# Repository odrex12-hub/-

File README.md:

//@version=5
indicator("Профессиональный Калькулятор v3.0", shorttitle="ProCalc Pro", overlay=true, max_labels_count=100)

// ========================
// НАСТРОЙКИ ОТОБРАЖЕНИЯ
// ========================
showTable := input.bool(true, "Показать таблицу")
showLabels := input.bool(true, "Показать метки")
showPlots := input.bool(false, "Показать графики")

// ========================
// ВИД КАЛЬКУЛЯТОРА
// ========================
calcType = input.string("Position Size", "🎯 Тип калькулятора", 
     options=["Position Size", "Risk/Reward", "Fibonacci", "Pivot Points", "Volatility", "Margin", "Portfolio Risk"])

// ========================
// ОБЩИЕ НАСТРОЙКИ
// ========================
// Автоматическое определение цен
useCurrentPrices = input.bool(true, "📊 Использовать текущие цены")

// Валютные пары и тип инструмента
instrumentType = input.string("Stock", "Тип инструмента", 
     options=["Stock", "Forex", "Crypto", "Futures", "Options"])

leverage = input.float(1.0, "Кредитное плечо", minval=1.0, maxval=100.0, step=0.5)

// ========================
// 1. УЛУЧШЕННЫЙ КАЛЬКУЛЯТОР РАЗМЕРА ПОЗИЦИИ
// ========================
if calcType == "Position Size"
    // Входные параметры
    depositSize = input.float(10000, "💰 Размер депозита ($)", minval=100, step=100)
    riskPerTrade = input.float(2.0, "⚠️ Риск на сделку (%)", minval=0.1, maxval=100, step=0.1)
    maxPortfolioRisk = input.float(20.0, "Макс. риск портфеля (%)", minval=5, maxval=100)
    
    // Автоматические цены
    autoEntry = useCurrentPrices ? close : na
    autoStop = useCurrentPrices ? low[1] : na
    
    entryPrice = input.float(autoEntry, "🎯 Цена входа", minval=0.00001)
    stopLoss = input.float(autoStop, "🛑 Цена стоп-лосса", minval=0.00001)
    takeProfit = input.float(na, "🎯 Цена тейк-профита", minval=0.00001)
    
    // Комиссии в зависимости от типа инструмента
    commissionType = input.string("Percent", "Тип комиссии", options=["Percent", "Fixed", "PerUnit"])
    
    commissionPercent = input.float(0.1, "Комиссия (%)", minval=0.0, step=0.01)
    commissionFixed = input.float(1.0, "Фиксированная комиссия ($)", minval=0.0, step=0.1)
    commissionPerUnit = input.float(0.01, "Комиссия за единицу", minval=0.0, step=0.001)
    
    // Скользящий стоп
    useTrailingStop = input.bool(false, "Использовать трейлинг-стоп")
    trailingDistance = input.float(2.0, "Дистанция трейлинга (%)", minval=0.1, step=0.1)
    
    // Расчеты с валидацией
    if entryPrice > 0 and stopLoss > 0
        // Проверка корректности входа
        if entryPrice <= stopLoss
            runtime.error("Для лонга цена входа должна быть ВЫШЕ стоп-лосса!")
        
        riskAmount := depositSize * (riskPerTrade / 100)
        priceRisk := math.abs(entryPrice - stopLoss)
        
        // Расчет размера позиции с учетом комиссии
        positionSizeBase := riskAmount / priceRisk
        
        // Учет комиссии
        if commissionType == "Percent"
            commissionCost := positionSizeBase * entryPrice * (commissionPercent / 100)
            effectivePositionSize := positionSizeBase
        else if commissionType == "Fixed"
            commissionCost := commissionFixed
            effectivePositionSize := (riskAmount - commissionCost) / priceRisk
        else
            commissionCost := positionSizeBase * commissionPerUnit
            effectivePositionSize := (riskAmount - commissionCost) / priceRisk
        
        positionSize := math.floor(effectivePositionSize)
        totalCost := positionSize * entryPrice + commissionCost
        positionPercent := (totalCost / depositSize) * 100
        
        // Расчет тейк-профита если задан
        if not na(takeProfit) and takeProfit > 0
            rewardAmount := math.abs(takeProfit - entryPrice) * positionSize
            rrRatio := rewardAmount / riskAmount
            winToBreakEven := (riskAmount / rewardAmount) * 100
        else
            rewardAmount := na
            rrRatio := na
            winToBreakEven := na
        
        // Трейлинг-стоп расчет
        if useTrailingStop
            trailStopPrice := entryPrice * (1 - trailingDistance / 100)
            trailDistance := math.abs(entryPrice - trailStopPrice)
        else
            trailStopPrice := na
        
        // Отображение
        if showLabels
            var label posLabel = label.new(bar_index, high * 1.02, "", 
                 color=color.new(color.blue, 90), textcolor=color.white, 
                 style=label.style_label_center, yloc=yloc.price,
                 size=size.normal)
            
            labelText = "🎯 РАСЧЕТ ПОЗИЦИИ\n" +
                 "═══════════════════\n" +
                 "📊 Тип: " + instrumentType + "\n" +
                 "💰 Депозит: $" + str.tostring(depositSize, "#,##0.00") + "\n" +
                 "⚠️ Риск: " + str.tostring(riskPerTrade, "#.#") + "% ($" + str.tostring(riskAmount, "#,##0.00") + ")\n" +
                 "🎯 Вход: $" + str.tostring(entryPrice, "#,##0." + str.tostring(math.max(2, math.ceil(math.log10(1/entryPrice))))) + "\n" +
                 "🛑 Стоп: $" + str.tostring(stopLoss, "#,##0." + str.tostring(math.max(2, math.ceil(math.log10(1/stopLoss))))) + "\n" +
                 "📈 Размер: " + str.tostring(positionSize, "#,##0") + " ед.\n" +
                 "💵 Стоимость: $" + str.tostring(totalCost, "#,##0.00") + "\n" +
                 "📊 % от депозита: " + str.tostring(positionPercent, "#.#") + "%\n" +
                 "💸 Комиссия: $" + str.tostring(commissionCost, "#,##0.00")
            
            if not na(takeProfit)
                labelText += "\n" +
                     "🎯 Тейк: $" + str.tostring(takeProfit, "#,##0.00") + "\n" +
                     "⚖️ R/R: " + str.tostring(rrRatio, "#.##") + ":1\n" +
                     "📈 Нужно побед: " + str.tostring(winToBreakEven, "#.#") + "%"
            
            if useTrailingStop
                labelText += "\n" +
                     "🎯 Трейлинг: $" + str.tostring(trailStopPrice, "#,##0.00")
            
            label.set_text(posLabel, labelText)
        
        // Табличное отображение
        if showTable
            var table posTable = table.new(position.top_right, 3, 15, 
                 bgcolor=color.new(color.blue, 95),
                 frame_color=color.blue,
                 frame_width=2)
            
            table.cell(posTable, 0, 0, "ПАРАМЕТР", text_color=color.white, bgcolor=color.blue)
            table.cell(posTable, 1, 0, "ЗНАЧЕНИЕ", text_color=color.white, bgcolor=color.blue)
            table.cell(posTable, 2, 0, "МЕТРИКА", text_color=color.white, bgcolor=color.blue)
            
            table.cell(posTable, 0, 1, "Депозит")
            table.cell(posTable, 1, 1, "$" + str.tostring(depositSize, "#,##0"))
            table.cell(posTable, 2, 1, "100%")
            
            table.cell(posTable, 0, 2, "Рик на сделку")
            table.cell(posTable, 1, 2, str.tostring(riskPerTrade, "#.#") + "%")
            table.cell(posTable, 2, 2, "$" + str.tostring(riskAmount, "#,##0"))
            
            table.cell(posTable, 0, 3, "Цена входа")
            table.cell(posTable, 1, 3, "$" + str.tostring(entryPrice, "#,##0.00"))
            table.cell(posTable, 2, 3, "")
            
            // ... и так далее для всех параметров

// ========================
// 2. РАСШИРЕННЫЙ RISK/REWARD
// ========================
else if calcType == "Risk/Reward"
    entryRR = input.float(close, "Цена входа")
    stopRR = input.float(low[1], "Стоп-лосс")
    targets = input.string("3", "Количество целей", options=["1", "2", "3", "4", "5"])
    
    numTargets = str.tonumber(targets)
    targetPrices = array.new_float()
    
    for i = 0 to numTargets - 1
        targetPrice = input.float(close * (1 + (i + 1) * 0.05), "Цель " + str.tostring(i + 1))
        array.push(targetPrices, targetPrice)
    
    risk = math.abs(entryRR - stopRR)
    
    // Расчет вероятности на основе волатильности
    atr20 = ta.atr(20)
    volatilityFactor = atr20 / close
    baseProbability = 0.5 // Базовая вероятность
    
    // Отображение с цветовой индикацией
    if showLabels
        var label rrLabel = label.new(bar_index, high * 1.02, "",
             color=color.new(color.purple, 90), textcolor=color.white,
             style=label.style_label_center, yloc=yloc.price)
        
        labelText = "⚖️ RISK/REWARD АНАЛИЗ\n" +
             "═══════════════════\n" +
             "Риск на сделку: $" + str.tostring(risk, "#.##") + "\n" +
             "ATR (20): " + str.tostring(atr20/close*100, "#.#") + "%\n" +
             "═══════════════════\n"
        
        for i = 0 to numTargets - 1
            targetPrice = array.get(targetPrices, i)
            reward = math.abs(targetPrice - entryRR)
            rrRatio = reward / risk
            probability = baseProbability * (1 / rrRatio) * (1 - volatilityFactor)
            
            // Цвет в зависимости от качества R/R
            rrColor = rrRatio >= 2 ? color.green : rrRatio >= 1.5 ? color.orange : color.red
            
            labelText += "Цель " + str.tostring(i + 1) + ": " + 
                 str.tostring(rrRatio, "#.##") + ":1 | " + 
                 str.tostring(probability * 100, "#.#") + "%\n" +
                 "$" + str.tostring(targetPrice, "#.##") + " (+" + 
                 str.tostring(reward, "#.##") + ")\n"

// ========================
// 6. КАЛЬКУЛЯТОР МАРЖИ (НОВЫЙ)
// ========================
else if calcType == "Margin"
    // Параметры для разных типов инструментов
    marginRequirements = input.float(50.0, "Требование маржи (%)", minval=1.0, maxval=100.0)
    positionMargin = input.float(10000.0, "Маржа позиции ($)", minval=100.0)
    
    // Расчет доступной маржи
    totalMargin = depositSize * leverage
    usedMargin = positionMargin
    freeMargin = totalMargin - usedMargin
    marginLevel = (totalMargin / usedMargin) * 100
    
    // Маржин колл уровни
    marginCallLevel = input.float(100.0, "Уровень маржин колла (%)", minval=50.0)
    stopOutLevel = input.float(50.0, "Уровень стоп-аута (%)", minval=20.0)
    
    // Цветовая индикация
    marginColor = marginLevel > 200 ? color.green : 
                  marginLevel > 150 ? color.orange : 
                  marginLevel > marginCallLevel ? color.yellow : color.red
    
    if showLabels
        var label marginLabel = label.new(bar_index, high * 1.02, "",
             color=color.new(marginColor, 90), textcolor=color.white,
             style=label.style_label_center, yloc=yloc.price)
        
        label.set_text(marginLabel,
             "🏦 РАСЧЕТ МАРЖИ\n" +
             "═══════════════════\n" +
             "Плечо: " + str.tostring(leverage, "#.#") + ":1\n" +
             "Общая маржа: $" + str.tostring(totalMargin, "#,##0") + "\n" +
             "Использовано: $" + str.tostring(usedMargin, "#,##0") + "\n" +
             "Свободно: $" + str.tostring(freeMargin, "#,##0") + "\n" +
             "Уровень маржи: " + str.tostring(marginLevel, "#.#") + "%\n" +
             "═══════════════════\n" +
             "Маржин колл: " + str.tostring(marginCallLevel, "#.#") + "%\n" +
             "Стоп аут: " + str.tostring(stopOutLevel, "#.#") + "%")

// ========================
// 7. РИСК ПОРТФЕЛЯ (НОВЫЙ)
// ========================
else if calcType == "Portfolio Risk"
    numPositions = input.int(5, "Количество позиций", minval=1, maxval=20)
    correlationMatrix = input.string("Low", "Корреляция портфеля", 
         options=["High", "Medium", "Low", "Diversified"])
    
    // Расчет VaR (Value at Risk)
    confidenceLevel = input.float(95.0, "Уровень доверия (%)", minval=90.0, maxval=99.9)
    timeHorizon = input.int(1, "Горизонт (дней)", minval=1, maxval=30)
    
    // Симуляция Монте-Карло (упрощенная)
    portfolioValue = depositSize
    portfolioVolatility = input.float(15.0, "Волатильность портф. (%)", minval=1.0, maxval=100.0)
    
    // Расчет VaR
    zScore = 1.96 // для 95%
    varValue = portfolioValue * (portfolioVolatility / 100) * zScore * math.sqrt(timeHorizon)
    
    // Максимальная просадка
    maxDrawdown = input.float(10.0, "Макс. просадка (%)", minval=1.0, maxval=50.0)
    
    // Шарп ратио
    expectedReturn = input.float(20.0, "Ожид. доходность (%)", minval=0.0, maxval=100.0)
    riskFreeRate = input.float(5.0, "Безриск. ставка (%)", minval=0.0, maxval=10.0)
    
    sharpeRatio = (expectedReturn - riskFreeRate) / portfolioVolatility
    
    if showLabels
        var label portfolioLabel = label.new(bar_index, high * 1.02, "",
             color=color.new(color.navy, 90), textcolor=color.white,
             style=label.style_label_center, yloc=yloc.price)
        
        label.set_text(portfolioLabel,
             "📊 АНАЛИЗ РИСКА ПОРТФЕЛЯ\n" +
             "══════════════════════\n" +
             "Позиций: " + str.tostring(numPositions) + "\n" +
             "Корреляция: " + correlationMatrix + "\n" +
             "Стоимость: $" + str.tostring(portfolioValue, "#,##0") + "\n" +
             "══════════════════════\n" +
             "VaR (" + str.tostring(confidenceLevel, "#.#") + "%, " + 
             str.tostring(timeHorizon) + "д): $" + str.tostring(varValue, "#,##0") + "\n" +
             "Макс. просадка: " + str.tostring(maxDrawdown, "#.#") + "%\n" +
             "══════════════════════\n" +
             "Шарп: " + str.tostring(sharpeRatio, "#.##") + "\n" +
             "Доходность: " + str.tostring(expectedReturn, "#.#") + "%\n" +
             "Волатильность: " + str.tostring(portfolioVolatility, "#.#") + "%")

// ========================
// ДОПОЛНИТЕЛЬНЫЕ ФУНКЦИИ
// ========================

// Алерты
if calcType == "Position Size" and positionPercent > 20
    alert("Внимание! Позиция превышает 20% от депозита", alert.freq_once_per_bar)

// Логирование в консоль
var string lastLog = ""
if ta.change(calcType)
    logText := "Калькулятор изменен на: " + calcType
    lastLog := logText
    // console.log(logText)

// Сохранение настроек
var string savedSettings = ""
saveSettings = input.bool(false, "Сохранить настройки")
if saveSettings
    savedSettings := "Deposit=" + str.tostring(depositSize) + 
                    ",Risk=" + str.tostring(riskPerTrade)

// ========================
// ВИЗУАЛЬНОЕ ОФОРМЛЕНИЕ
// ========================

// Цветовая схема в зависимости от типа
getCalcColor(type) =>
    switch type
        "Position Size" => color.blue
        "Risk/Reward" => color.purple
        "Fibonacci" => color.orange
        "Pivot Points" => color.green
        "Volatility" => color.red
        "Margin" => color.teal
        "Portfolio Risk" => color.navy
        => color.gray

// Графическое отображение
if showPlots
    plotColor = getCalcColor(calcType)
    
    if calcType == "Pivot Points"
        plot(pivot, "Pivot", plotColor, 2)
        plot(r1, "R1", color.red, 1)
        plot(s1, "S1", color.green, 1)
    
    if calcType == "Fibonacci"
        for i = 0 to 4
            fibValue = array.get(fibLevels, i)
            plot(fibValue, "Fib " + str.tostring(i), plotColor, 1)

// Статистика использования
var int useCount = 0
if ta.change(calcType)
    useCount += 1

// Футер с информацией
if showLabels
    var label footerLabel = label.new(bar_index, low * 0.98, "",
         color=color.new(color.gray, 90), textcolor=color.white,
         style=label.style_label_center, yloc=yloc.price,
         size=size.small)
    
    label.set_text(footerLabel,
         "ProCalc v3.0 | Использован: " + str.tostring(useCount) + " раз | " +
         "Bar: " + str.tostring(bar_index) + " | " +
         "Время: " + str.tostring(hour, "00") + ":" + str.tostring(minute, "00"))

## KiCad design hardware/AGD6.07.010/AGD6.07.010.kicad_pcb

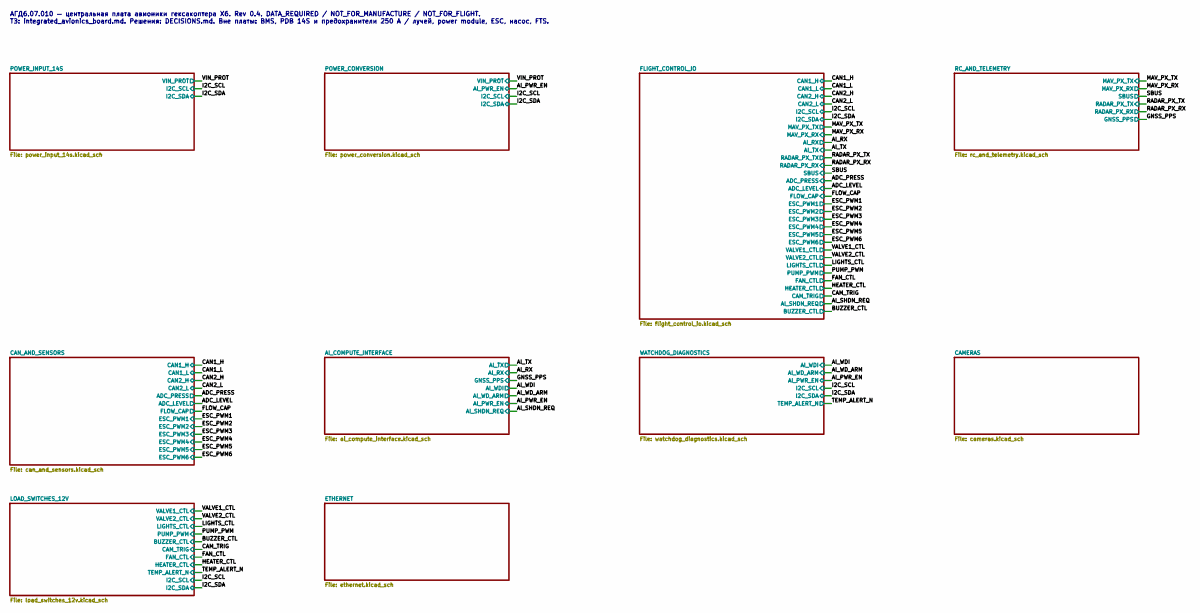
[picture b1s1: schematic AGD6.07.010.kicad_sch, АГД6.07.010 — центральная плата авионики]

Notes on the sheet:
АГД6.07.010 — центральная плата авионики гексакоптера X6. Rev 0.4. DATA_REQUIRED / NOT_FOR_MANUFACTURE / NOT_FOR_FLIGHT. ТЗ: integrated_avionics_board.md. Решения: DECISIONS.md. Вне платы: BMS, PDB 14S и предохранители 250 A / лучей, power module, ESC, насос, FTS.

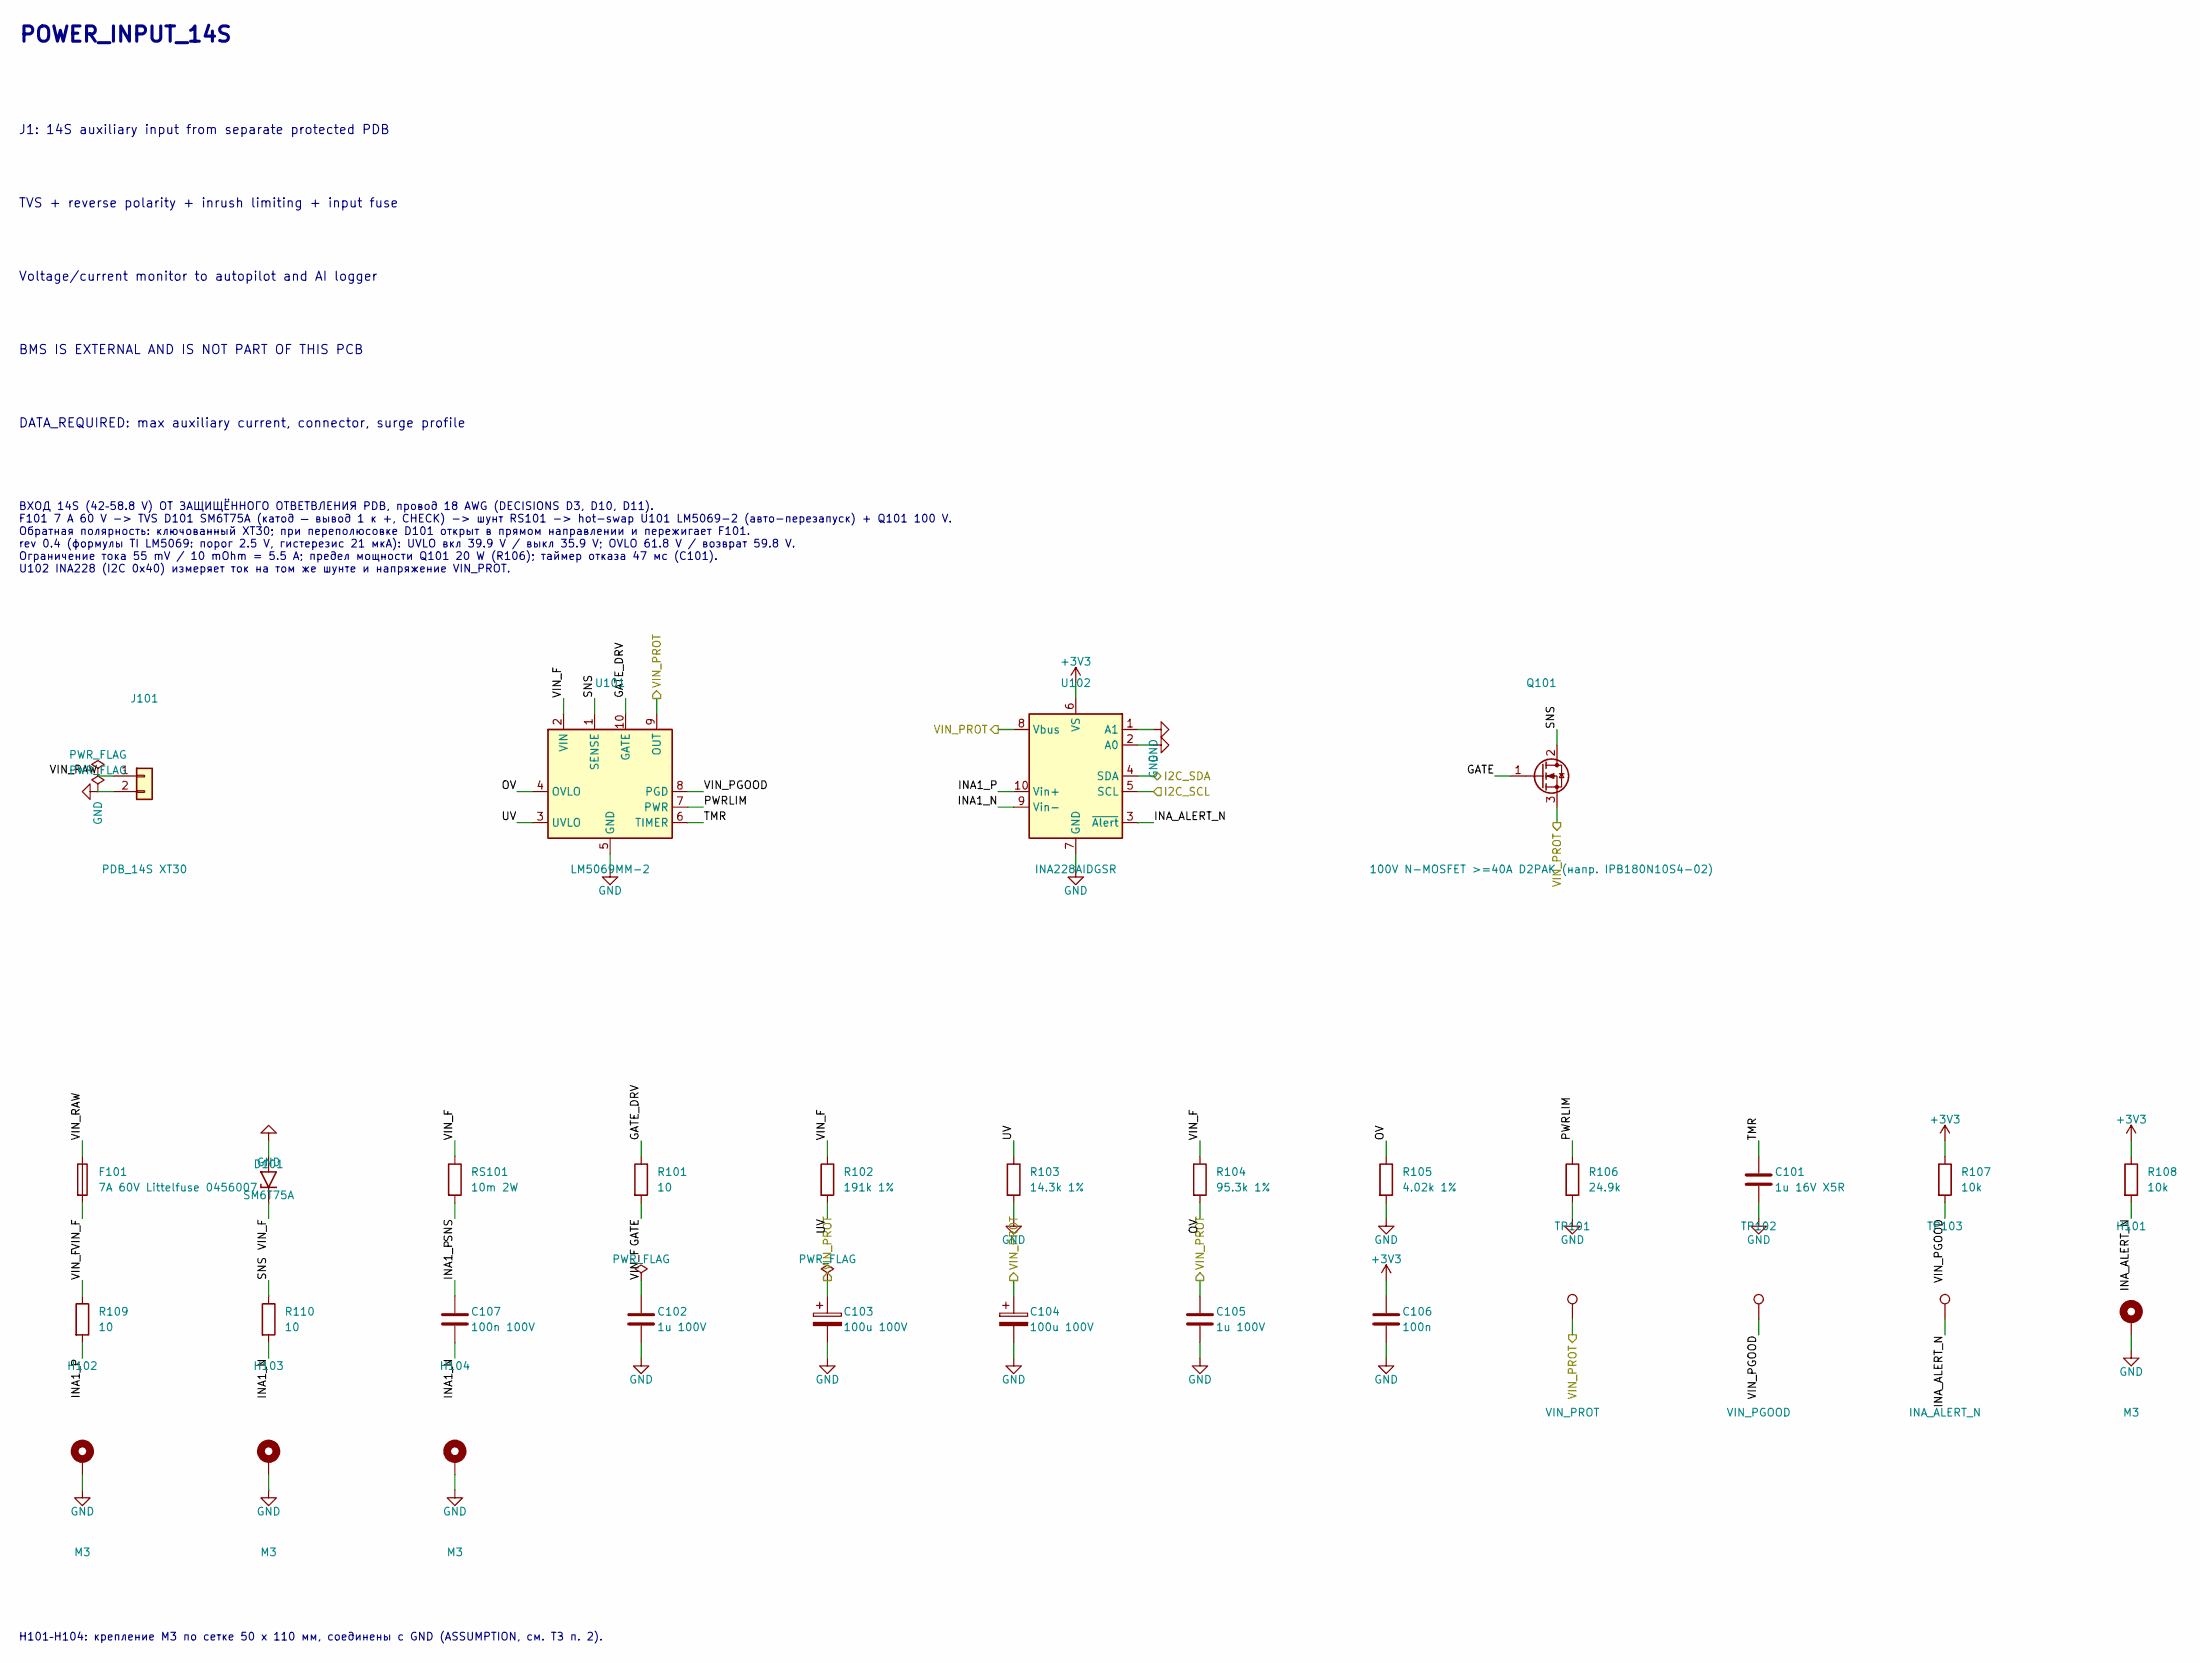
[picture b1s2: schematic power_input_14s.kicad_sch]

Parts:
C101: 1u 16V X5R; C_0402_1005Metric
C102, C105: 1u 100V; C_1210_3225Metric
C103, C104: 100u 100V; CP_Elec_10x10.5
C106: 100n; C_0402_1005Metric
C107: 100n 100V; C_0603_1608Metric
D101: SM6T75A; D_SMB
F101: 7A 60V Littelfuse 0456007; Fuse_Littelfuse-NANO2-451_453
H101, H102, H103, H104: M3; MountingHole_3.2mm_M3_Pad_Via
J101: PDB_14S XT30; AMASS_XT30PW-M_1x02_P2.50mm_Horizontal
Q101: 100V N-MOSFET >=40A D2PAK (напр. IPB180N10S4-02); TO-263-2
R101: 10; R_0402_1005Metric
R102: 191k 1%; R_0603_1608Metric
R103: 14.3k 1%; R_0603_1608Metric
R104: 95.3k 1%; R_0603_1608Metric
R105: 4.02k 1%; R_0603_1608Metric
R106: 24.9k; R_0402_1005Metric
R107, R108: 10k; R_0402_1005Metric
R109, R110: 10; R_0603_1608Metric
RS101: 10m 2W; R_2512_6332Metric
TP101: VIN_PROT; TestPoint_Pad_D1.5mm
TP102: VIN_PGOOD; TestPoint_Pad_D1.5mm
TP103: INA_ALERT_N; TestPoint_Pad_D1.5mm
U101: LM5069MM-2; MSOP-10_3x3mm_P0.5mm
U102: INA228AIDGSR; TSSOP-10_3x3mm_P0.5mm

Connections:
+3V3: C106.1, R107.1, R108.1, U102.6 (VS); also elsewhere on the board
/I2C_SCL: U102.5 (SCL); also elsewhere on the board
/I2C_SDA: U102.4 (SDA); also elsewhere on the board
/POWER_INPUT_14S/GATE: Q101.1 (G), R101.2
/POWER_INPUT_14S/GATE_DRV: R101.1, U101.10 (GATE)
/POWER_INPUT_14S/INA1_N: C107.2, R110.2, U102.9 (Vin-)
/POWER_INPUT_14S/INA1_P: C107.1, R109.2, U102.10 (Vin+)
/POWER_INPUT_14S/INA_ALERT_N: R108.2, TP103.1, U102.3 (~Alert)
/POWER_INPUT_14S/OV: R104.2, R105.1, U101.4 (OVLO)
/POWER_INPUT_14S/PWRLIM: R106.1, U101.7 (PWR)
/POWER_INPUT_14S/SNS: Q101.2 (D), R110.1, RS101.2, U101.1 (SENSE)
/POWER_INPUT_14S/TMR: C101.1, U101.6 (TIMER)
/POWER_INPUT_14S/UV: R102.2, R103.1, U101.3 (UVLO)
/POWER_INPUT_14S/VIN_F: C102.1, D101.1 (A1), F101.2, R102.1, R104.1, R109.1, RS101.1, U101.2 (VIN)
/POWER_INPUT_14S/VIN_PGOOD: R107.2, TP102.1, U101.8 (PGD)
/POWER_INPUT_14S/VIN_RAW: F101.1, J101.1
/VIN_PROT: C103.1, C104.1, C105.1, Q101.3 (S), TP101.1, U101.9 (OUT), U102.8 (Vbus); also elsewhere on the board
GND: C101.2, C102.2, C103.2, C104.2, C105.2, C106.2, D101.2 (A2), H101.1, H102.1, H103.1, H104.1, J101.2, R103.2, R105.2, R106.2, U101.5 (GND), U102.1 (A1), U102.2 (A0), U102.7 (GND); also elsewhere on the board

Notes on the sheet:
BMS IS EXTERNAL AND IS NOT PART OF THIS PCB
TVS + reverse polarity + inrush limiting + input fuse
POWER_INPUT_14S
DATA_REQUIRED: max auxiliary current, connector, surge profile
Voltage/current monitor to autopilot and AI logger
J1: 14S auxiliary input from separate protected PDB
ВХОД 14S (42–58.8 V) ОТ ЗАЩИЩЁННОГО ОТВЕТВЛЕНИЯ PDB, провод 18 AWG (DECISIONS D3, D10, D11). F101 7 A 60 V -> TVS D101 SM6T75A (катод — вывод 1 к +, CHECK) -> шунт RS101 -> hot-swap U101 LM5069-2 (авто-перезапуск) + Q101 100 V. Обратная полярность: ключованный XT30; при переполюсовке D101 открыт в 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
H101–H104: крепление M3 по сетке 50 x 110 мм, соединены с GND (ASSUMPTION, см. ТЗ п. 2).

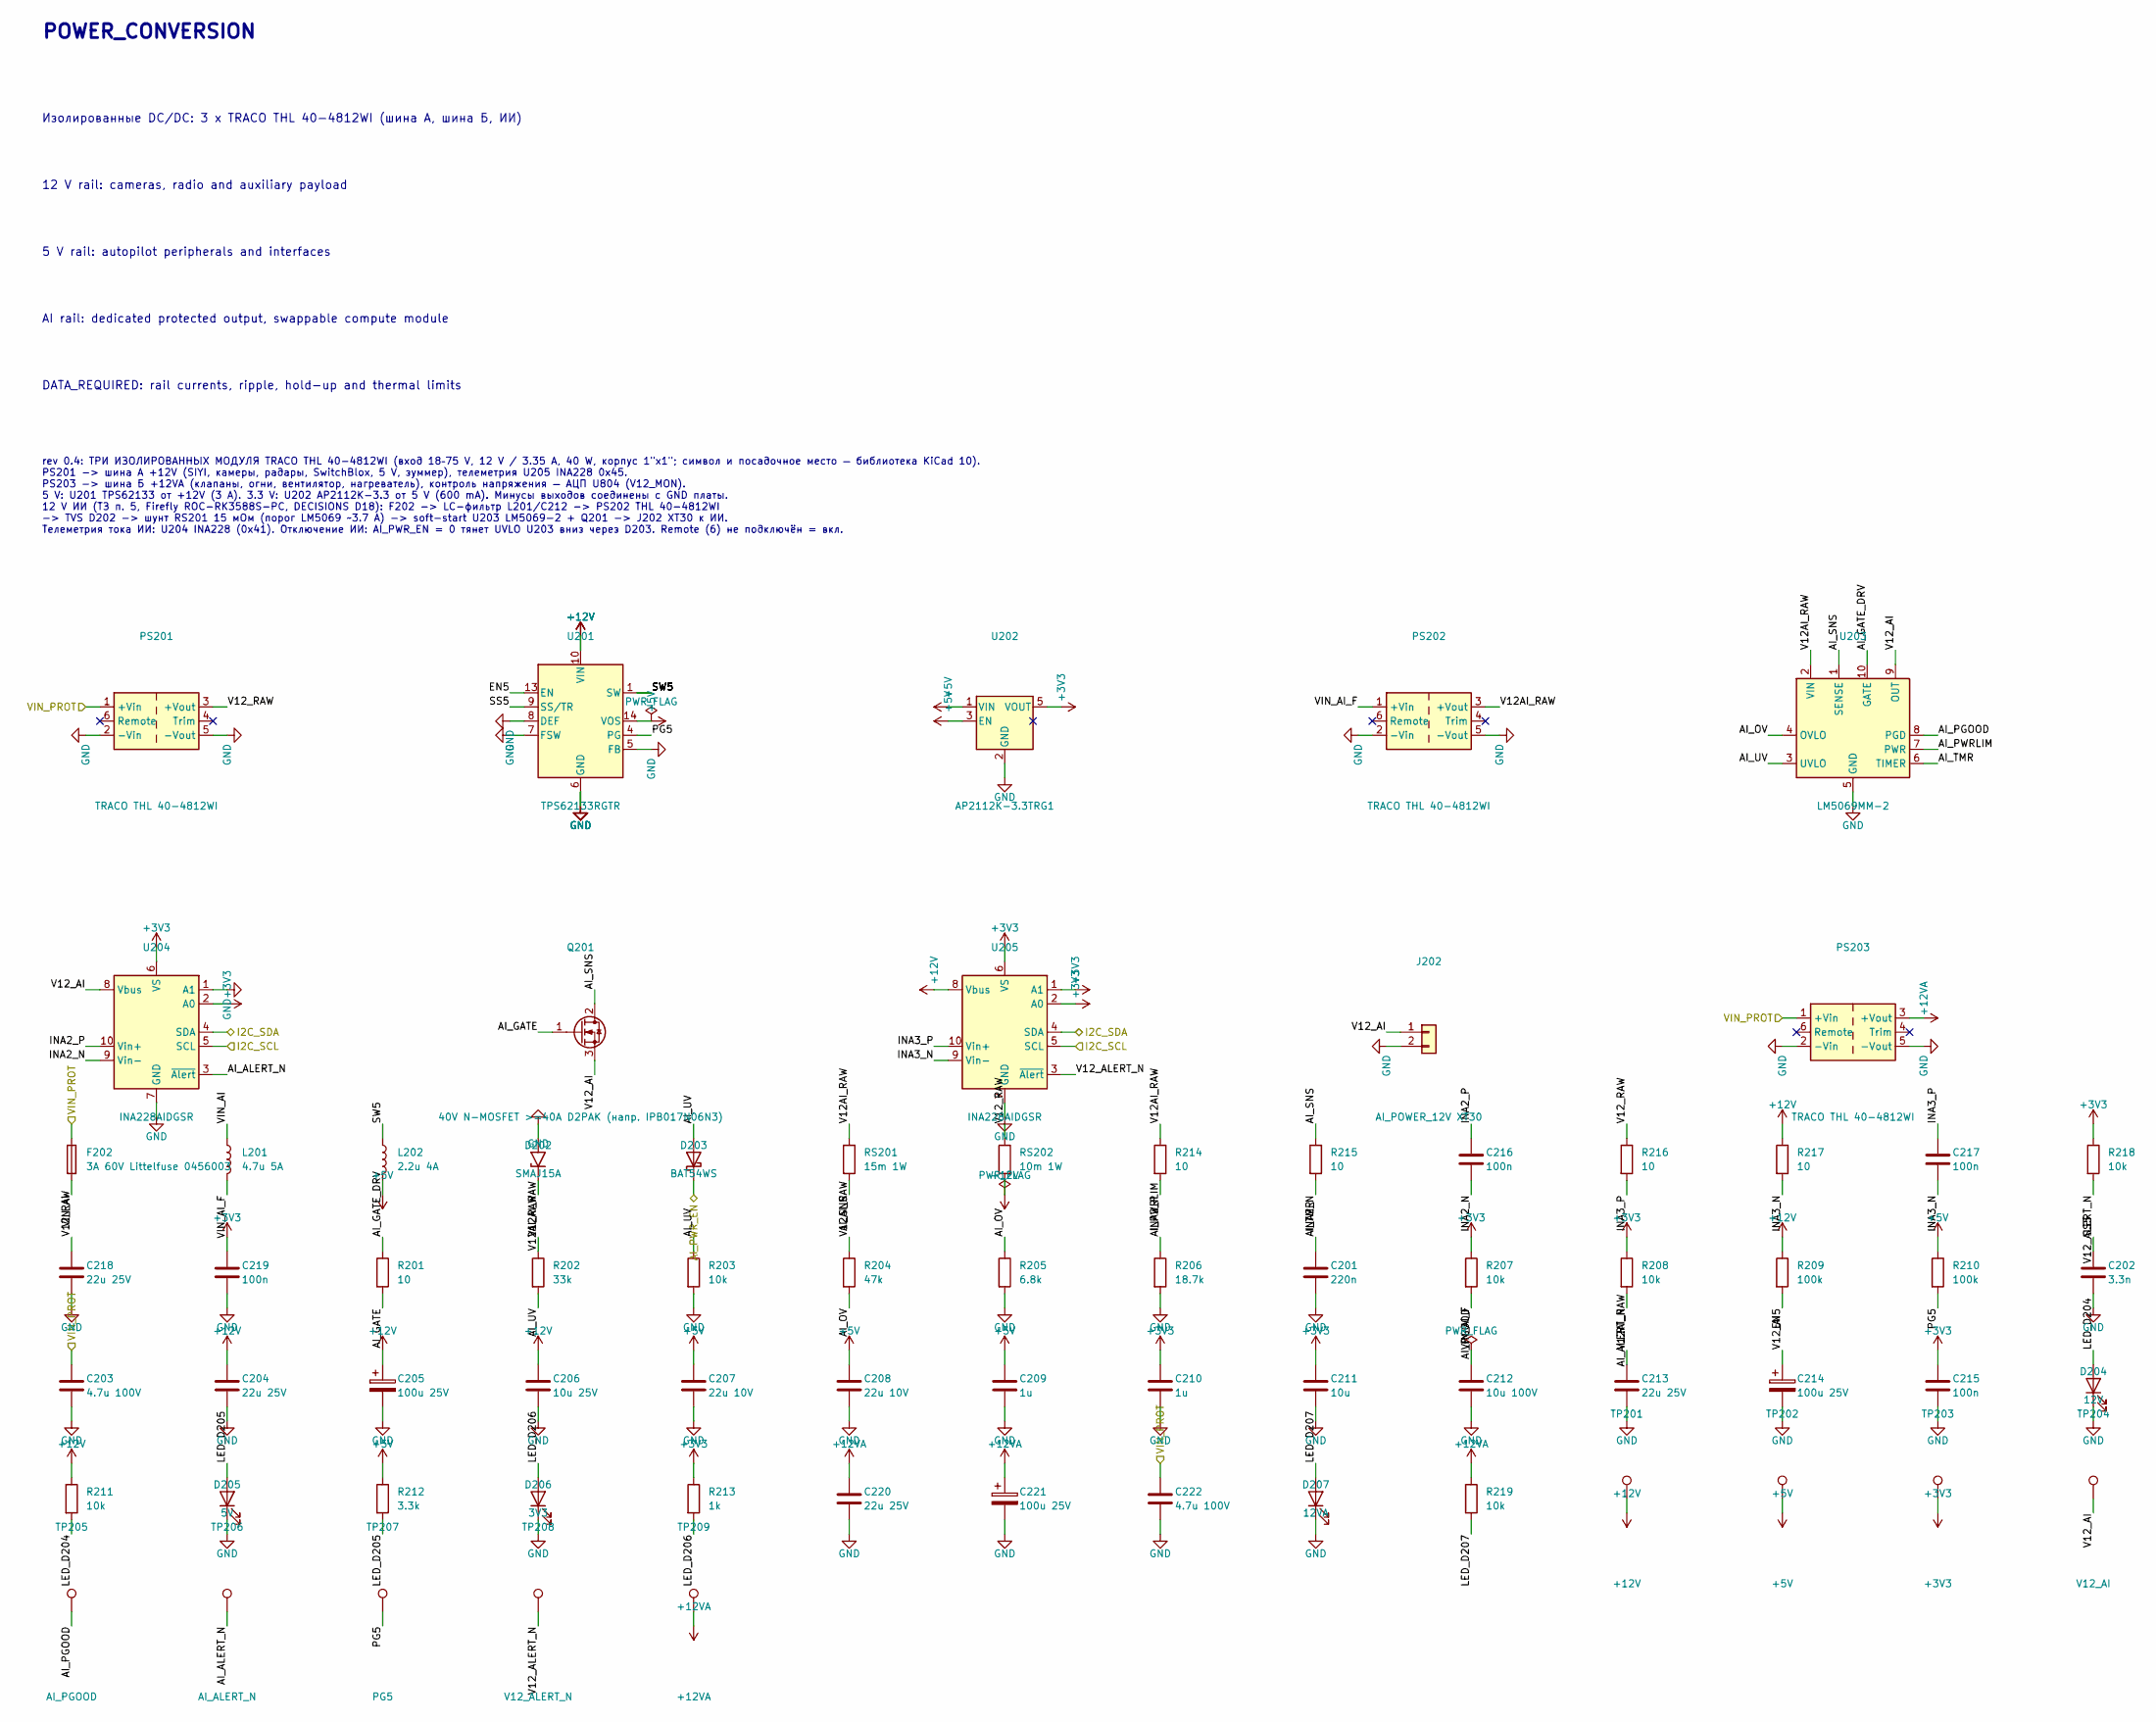
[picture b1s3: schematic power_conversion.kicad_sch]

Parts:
C201: 220n; C_0402_1005Metric
C202: 3.3n; C_0402_1005Metric
C203, C222: 4.7u 100V; C_1210_3225Metric
C204, C213, C218, C220: 22u 25V; C_1210_3225Metric
C205, C214, C221: 100u 25V; CP_Elec_10x10.5
C206: 10u 25V; C_0805_2012Metric
C207, C208: 22u 10V; C_0805_2012Metric
C209, C210: 1u; C_0603_1608Metric
C211: 10u; C_0805_2012Metric
C212: 10u 100V; C_1210_3225Metric
C215, C219: 100n; C_0402_1005Metric
C216, C217: 100n; C_0603_1608Metric
D202: SMAJ15A; D_SMA
D203: BAT54WS; D_SOD-323
D204: 12V; LED_0603_1608Metric
D205: 5V; LED_0603_1608Metric
D206: 3V3; LED_0603_1608Metric
D207: 12VA; LED_0603_1608Metric
F202: 3A 60V Littelfuse 0456003; Fuse_Littelfuse-NANO2-451_453
J202: AI_POWER_12V XT30; AMASS_XT30PW-F_1x02_P2.50mm_Horizontal
L201: 4.7u 5A; L_Bourns_SRP1245A
L202: 2.2u 4A; L_Bourns_SRP5030T
PS201, PS202, PS203: TRACO THL 40-4812WI; Converter_DCDC_TRACO_THL40-xxxxWI_THT
Q201: 40V N-MOSFET >=40A D2PAK (напр. IPB017N06N3); TO-263-2
R201: 10; R_0402_1005Metric
R202: 33k; R_0402_1005Metric
R203, R207, R208, R211, R218, R219: 10k; R_0402_1005Metric
R204: 47k; R_0402_1005Metric
R205: 6.8k; R_0402_1005Metric
R206: 18.7k; R_0402_1005Metric
R209, R210: 100k; R_0402_1005Metric
R212: 3.3k; R_0402_1005Metric
R213: 1k; R_0402_1005Metric
R214, R215, R216, R217: 10; R_0603_1608Metric
RS201: 15m 1W; R_2512_6332Metric
RS202: 10m 1W; R_2512_6332Metric
TP201: +12V; TestPoint_Pad_D1.5mm
TP202: +5V; TestPoint_Pad_D1.5mm
TP203: +3V3; TestPoint_Pad_D1.5mm
TP204: V12_AI; TestPoint_Pad_D1.5mm
TP205: AI_PGOOD; TestPoint_Pad_D1.5mm
TP206: AI_ALERT_N; TestPoint_Pad_D1.5mm
TP207: PG5; TestPoint_Pad_D1.5mm
TP208: V12_ALERT_N; TestPoint_Pad_D1.5mm
TP209: +12VA; TestPoint_Pad_D1.5mm
U201: TPS62133RGTR; VQFN-16-1EP_3x3mm_P0.5mm_EP1.68x1.68mm_ThermalVias
U202: AP2112K-3.3TRG1; SOT-23-5
U203: LM5069MM-2; MSOP-10_3x3mm_P0.5mm
U204, U205: INA228AIDGSR; TSSOP-10_3x3mm_P0.5mm

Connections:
+3V3: C210.1, C211.1, C215.1, C219.1, R207.1, R208.1, R213.1, R218.1, TP203.1, U202.5 (VOUT), U204.2 (A0), U204.6 (VS), U205.1 (A1), U205.2 (A0), U205.6 (VS); also elsewhere on the board
+5V: C207.1, C208.1, C209.1, L202.2, R210.1, R212.1, TP202.1, U201.14 (VOS), U202.1 (VIN), U202.3 (EN); also elsewhere on the board
+12V: C204.1, C205.1, C206.1, R209.1, R211.1, R217.1, RS202.2, TP201.1, U201.10 (VIN), U201.11 (VIN), U201.12 (VIN), U205.8 (Vbus); also elsewhere on the board
+12VA: C220.1, C221.1, PS203.3 (+Vout), R219.1, TP209.1; also elsewhere on the board
/AI_PWR_EN: D203.1 (K); also elsewhere on the board
/I2C_SCL: U204.5 (SCL), U205.5 (SCL); also elsewhere on the board
/I2C_SDA: U204.4 (SDA), U205.4 (SDA); also elsewhere on the board
/POWER_CONVERSION/AI_ALERT_N: R208.2, TP206.1, U204.3 (~Alert)
/POWER_CONVERSION/AI_GATE: Q201.1 (G), R201.2
/POWER_CONVERSION/AI_GATE_DRV: R201.1, U203.10 (GATE)
/POWER_CONVERSION/AI_OV: R204.2, R205.1, U203.4 (OVLO)
/POWER_CONVERSION/AI_PGOOD: R207.2, TP205.1, U203.8 (PGD)
/POWER_CONVERSION/AI_PWRLIM: R206.1, U203.7 (PWR)
/POWER_CONVERSION/AI_SNS: Q201.2 (D), R215.1, RS201.2, U203.1 (SENSE)
/POWER_CONVERSION/AI_TMR: C201.1, U203.6 (TIMER)
/POWER_CONVERSION/AI_UV: D203.2 (A), R202.2, R203.1, U203.3 (UVLO)
/POWER_CONVERSION/EN5: R209.2, U201.13 (EN)
/POWER_CONVERSION/INA2_N: C216.2, R215.2, U204.9 (Vin-)
/POWER_CONVERSION/INA2_P: C216.1, R214.2, U204.10 (Vin+)
/POWER_CONVERSION/INA3_N: C217.2, R217.2, U205.9 (Vin-)
/POWER_CONVERSION/INA3_P: C217.1, R216.2, U205.10 (Vin+)
/POWER_CONVERSION/LED_D204: D204.2 (A), R211.2
/POWER_CONVERSION/LED_D205: D205.2 (A), R212.2
/POWER_CONVERSION/LED_D206: D206.2 (A), R213.2
/POWER_CONVERSION/LED_D207: D207.2 (A), R219.2
/POWER_CONVERSION/PG5: R210.2, TP207.1, U201.4 (PG)
/POWER_CONVERSION/SS5: C202.1, U201.9 (SS/TR)
/POWER_CONVERSION/SW5: L202.1, U201.1 (SW), U201.2 (SW), U201.3 (SW)
/POWER_CONVERSION/V12AI_RAW: C213.1, D202.1 (A1), PS202.3 (+Vout), R202.1, R204.1, R214.1, RS201.1, U203.2 (VIN)
/POWER_CONVERSION/V12_AI: C214.1, J202.1, Q201.3 (S), TP204.1, U203.9 (OUT), U204.8 (Vbus)
/POWER_CONVERSION/V12_ALERT_N: R218.2, TP208.1, U205.3 (~Alert)
/POWER_CONVERSION/V12_RAW: C218.1, PS201.3 (+Vout), R216.1, RS202.1
/POWER_CONVERSION/VIN_AI: F202.2, L201.1
/POWER_CONVERSION/VIN_AI_F: C212.1, L201.2, PS202.1 (+Vin)
/VIN_PROT: C203.1, C222.1, F202.1, PS201.1 (+Vin), PS203.1 (+Vin); also elsewhere on the board
GND: C201.2, C202.2, C203.2, C204.2, C205.2, C206.2, C207.2, C208.2, C209.2, C210.2, C211.2, C212.2, C213.2, C214.2, C215.2, C218.2, C219.2, C220.2, C221.2, C222.2, D202.2 (A2), D204.1 (K), D205.1 (K), D206.1 (K), D207.1 (K), J202.2, PS201.2 (-Vin), PS201.5 (-Vout), PS202.2 (-Vin), PS202.5 (-Vout), PS203.2 (-Vin), PS203.5 (-Vout), R203.2, R205.2, R206.2, U201.5 (FB), U201.6 (GND), U201.7 (FSW), U201.8 (DEF), U201.15 (GND), U201.16 (GND), U201.17 (GND), U202.2 (GND), U203.5 (GND), U204.1 (A1), U204.7 (GND), U205.7 (GND); also elsewhere on the board

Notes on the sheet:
Изолированные DC/DC: 3 x TRACO THL 40-4812WI (шина А, шина Б, ИИ)
AI rail: dedicated protected output, swappable compute module
5 V rail: autopilot peripherals and interfaces
12 V rail: cameras, radio and auxiliary payload
DATA_REQUIRED: rail currents, ripple, hold-up and thermal limits
POWER_CONVERSION
rev 0.4: ТРИ ИЗОЛИРОВАННЫХ МОДУЛЯ TRACO THL 40-4812WI (вход 18–75 V, 12 V / 3.35 A, 40 W, корпус 1"x1"; символ и посадочное место — библиотека KiCad 10). PS201 -> шина А +12V (SIYI, камеры, радары, SwitchBlox, 5 V, зуммер), телеметрия U205 INA228 0x45. PS203 -> шина Б +12VA (клапаны, огни, вентилят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
